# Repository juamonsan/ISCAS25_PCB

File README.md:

# ISCAS25_PCB
 PCB that also serves as a pen holder in conmemoration of ISCAS 2025. Made with [KiCAD](https://www.kicad.org/), [Inkscape](https://inkscape.org/) and [Gingerbread](https://github.com/wntrblm/Gingerbread).

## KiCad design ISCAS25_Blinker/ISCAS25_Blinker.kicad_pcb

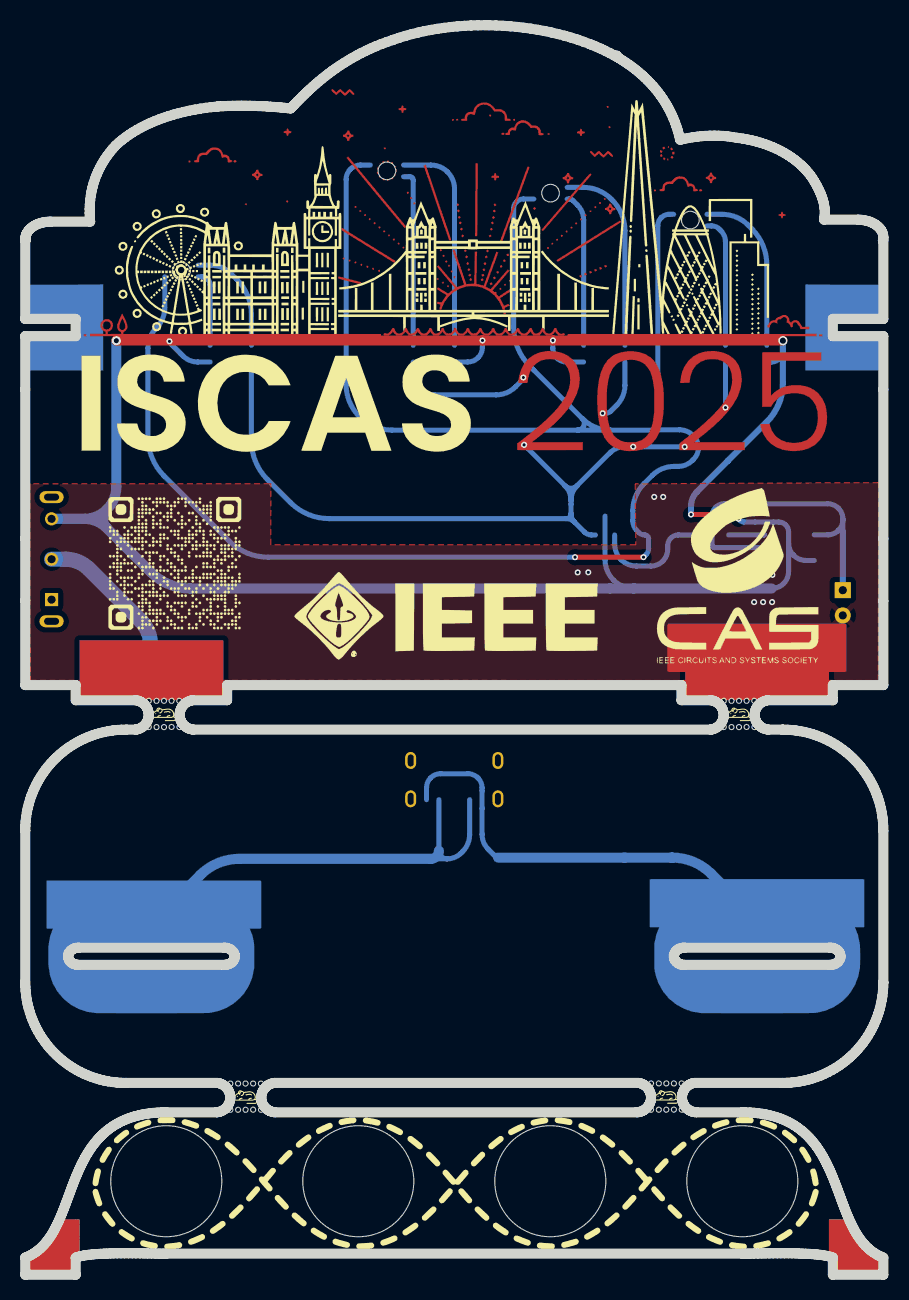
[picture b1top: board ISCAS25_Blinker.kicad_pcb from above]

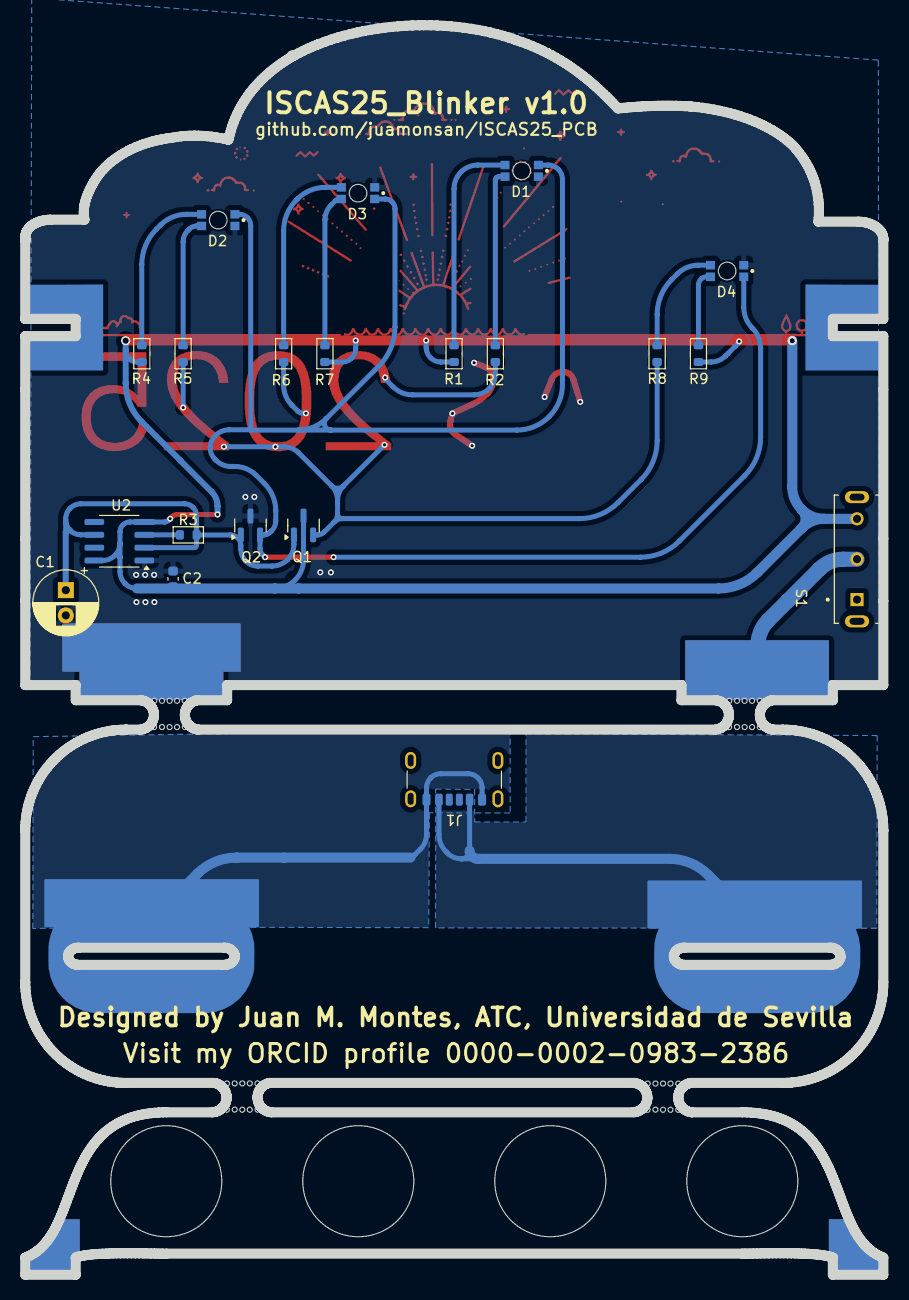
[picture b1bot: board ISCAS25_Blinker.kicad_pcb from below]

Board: 2 copper layers, 85.0 x 123.8 mm, 25 parts (20 on the bottom side), 15 nets.

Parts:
C1: 220uF; CP_Radial_D6.3mm_P2.50mm
C2: 0.1uF; C_0603_1608Metric
D1, D2, D3, D4: Red & Blue, 120°; WL-SBRW_1205_reverse mount
J1: USB_C_Receptacle_PowerOnly_6P; USB_C_Receptacle_GCT_USB4125-xx-x-0190_6P_TopMnt_Horizontal
Q1: BC846; SOT-23
Q2: BC857; SOT-23
QR: QR; LOGO
R1, R2, R4, R5, R6, R7, R8, R9: 470; R_0603_1608Metric
R3: 1k; R_0603_1608Metric
S1: SLW-1277545-3A-RA-N-D; SW_SLW-1277545-3A-RA-N-D
U2: NE555D; SOIC-8_3.9x4.9mm_P1.27mm
mouse-bite-3mm-6mm, mouse-bite-3mm-6mm#2, mouse-bite-3mm-6mm#3, mouse-bite-3mm-6mm#4: VAL**; mouse-bite-3mm-6mm

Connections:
+5V: C2.1, Q1.3 (C), R1.1, R4.1, R7.1, R9.1, S1.3, U2.4 (R), U2.8 (VCC)
/LED_1_Driver: D1.2 (K), D2.2 (K), D3.1 (K), D4.1 (K), Q2.2 (E)
/LED_2_Driver: Q1.2 (E), R2.1, R5.1, R6.1, R8.1
GND: C1.2, C2.2, D1.1 (K), D2.1 (K), D3.2 (K), D4.2 (K), J1.A12 (GND), J1.B12 (GND), Q2.3 (C), U2.1 (GND)
unnamed: D1.3 (A), R1.2
unnamed: D1.4 (A), R2.2
unnamed: D2.3 (A), R4.2
unnamed: D2.4 (A), R5.2
unnamed: D3.3 (A), R6.2
unnamed: D3.4 (A), R7.2
unnamed: D4.3 (A), R8.2
unnamed: D4.4 (A), R9.2
unnamed: J1.A9 (VBUS), J1.B9 (VBUS), S1.2
unnamed: C1.1, Q1.1 (B), Q2.1 (B), R3.2, U2.2 (TR), U2.6 (THR)
unnamed: R3.1, U2.3 (Q)

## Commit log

2025-05-05 Schematic done
2025-05-05 Fixed aux PCBs
2025-05-05 Components added to PCB
2025-05-06 Finished but not panelized
2025-05-06 Final assembly
2025-05-16 Changes in BOM information
